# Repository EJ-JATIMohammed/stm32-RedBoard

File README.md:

# STM32 RedBoard

Custom STM32F103C8T6 development board designed with KiCad, featuring USB-C, Micro-USB, CAN, Micro-SD, SWD and GPIO interfaces.

## Overview

The STM32 RedBoard is an open-source hardware development platform built around the ARM Cortex-M3-based STM32F103C8T6 microcontroller. The board integrates multiple connectivity options and interfaces, designed for embedded systems development, prototyping, and educational projects using professional-grade open-source tools.

## Features

- **Microcontroller**: ARM Cortex-M3 STM32F103C8T6 (72 MHz)
- **Memory**: 256 KB Flash, 64 KB SRAM
- **Connectivity**: USB-C and Micro-USB interfaces, CAN 2.0B support, Micro-SD card interface
- **Debugging**: Serial Wire Debug (SWD) interface for real-time debugging and firmware upload
- **Expansion**: GPIO pins for sensor integration and custom applications
- **Design**: Professional schematic and PCB layout in KiCad 10.0

## Hardware Specifications

| Specification | Value |
|---|---|
| Microcontroller | STM32F103C8T6 (ARM Cortex-M3, 72 MHz) |
| Flash Memory | 256 KB |
| SRAM | 64 KB |
| Supply Voltage | 3.3V (USB or external) |
| Interfaces | USB-C, Micro-USB, CAN, SWD, Micro-SD, GPIO |
| EDA Tool | KiCad 10.0 |

## Interfaces

### USB-C (Primary Interface)
USB Type-C 2.0 interface for primary power supply and data communication. Features reversible plug orientation and robust mechanical connection.

### Micro-USB (Secondary Interface)
USB Micro Type-B connector for alternative power and communication. Provides legacy compatibility and additional charging capability.

### CAN Bus
CAN 2.0B protocol support for vehicle diagnostics, industrial automation, and real-time control systems. Uses differential signaling with CAN_H and CAN_L lines.

### Micro-SD Card Interface
8-pin Micro SD Card Socket supporting SDIO/SPI modes. Enables data storage, firmware updates, and data logging applications.

### SWD (Serial Wire Debug)
ARM Serial Wire Debug interface for real-time debugging and firmware programming. Compatible with ST-LINK/V2, Segger J-Link, and OpenOCD-compatible debuggers.

### GPIO Expansion
Multiple GPIO pins from the STM32F103C8T6 with 3.3V logic levels (5V tolerant on selected pins). Supports digital I/O, PWM, analog input (ADC), and timer functions.

## Hardware Design

The STM32 RedBoard is fully designed in **KiCad 10.0**, a professional, open-source electronic design automation suite supporting Windows, macOS, and Linux.

### Design Files

| File | Description |
|---|---|
| `kicad_files/stm32f013 Red board.kicad_sch` | Main schematic with all component connections and interfaces |
| `kicad_files/Block_Diagram.kicad_sch` | High-level system architecture overview |
| `kicad_files/stm32f013 Red board.kicad_pcb` | PCB layout, routing, and component placement |
| `kicad_files/stm32f013 Red board.kicad_pro` | KiCad project file |

## PCB Images

Representative design documentation images:

## Repository Structure

```
stm32-RedBoard/
├── README.md                                        # Project documentation
├── LICENSE                                          # MIT License
├── PCB_images/                                      # Design documentation images
│   ├── 1.png
│   ├── 2.png
│   ├── 3.png
│   ├── 4.png
│   ├── 5.png
│   ├── 6.png
│   └── 7.png
├── Shematics/                                       # Schematic PDF export
│   └── stm32f013 Red board-Stm32_Red_Board.pdf
└── kicad_files/                                     # KiCad project files
    ├── Block_Diagram.kicad_sch
    ├── Stm32_Red_Board.kicad_sch
    ├── stm32f013 Red board.kicad_sch
    ├── stm32f013 Red board.kicad_pcb
    ├── stm32f013 Red board.kicad_pro
    ├── stm32f013 Red board.kicad_prl
    ├── stm32f013 Red board-Stm32_Red_Board.pdf
    └── _restore_backup_*/ (version control backups)
```

## Getting Started

### Prerequisites

- **KiCad 10.0 or later** – Download from [kicad.org](https://www.kicad.org)
- **Git** (optional, for cloning the repository)

### Opening the Project

1. **Clone the repository**
   ```bash
   git clone https://github.com/EJ-JATIMohammed/stm32-RedBoard.git
   cd stm32-RedBoard
   ```

2. **Open in KiCad**
   - Launch KiCad
   - Select **File** → **Open Project**
   - Navigate to `kicad_files/stm32f013 Red board.kicad_pro`

3. **Explore the design**
   - **Schematic**: View connections and component values
   - **PCB Layout**: Review trace routing and layer assignments
   - **Block Diagram**: See `Block_Diagram.kicad_sch` for system overview
   - **3D Viewer**: View → 3D Viewer for mechanical review

### Design Tools

- **Electrical Rules Check (ERC)**: Tools → Electrical Rules Checker
- **Design Rules Check (DRC)**: Tools → Design Rules Checker
- **Manufacturing Files**: File → Plot to generate Gerber files

## Programming and Debugging

### Supported Debuggers

- **ST-LINK/V2** – Official STMicroelectronics debugger
- **Segger J-Link** – Universal JTAG/SWD debugger
- **OpenOCD** – Open-source debugging protocol

### Development Environments

- **STM32CubeIDE** – Official STMicroelectronics IDE
- **STM32CubeMX** – Configuration and code generation
- **VSCode + ARM Toolchain** – Open-source workflow
- **PlatformIO** – Cross-platform embedded development

## Future Improvements

- **Documentation**: Detailed pinout assignments, bill of materials (BOM), assembly guide
- **Firmware Examples**: USB drivers, CAN bus applications, Micro-SD file system integration, GPIO and ADC samples
- **Hardware Validation**: Prototype fabrication and functional testing
- **Design Enhancements**: 3D STEP models, EMC/EMI review, power distribution optimization

## License

This project is released under the **MIT License**. See [LICENSE](LICENSE) for complete terms.

## Author

**EJ-JATI Mohammed**  
GitHub: [EJ-JATIMohammed](https://github.com/EJ-JATIMohammed)  
Repository: [stm32-RedBoard](https://github.com/EJ-JATIMohammed/stm32-RedBoard)

---

**Project Created**: August 2026  
**Last Updated**: October 2026  
**KiCad Version**: 10.0

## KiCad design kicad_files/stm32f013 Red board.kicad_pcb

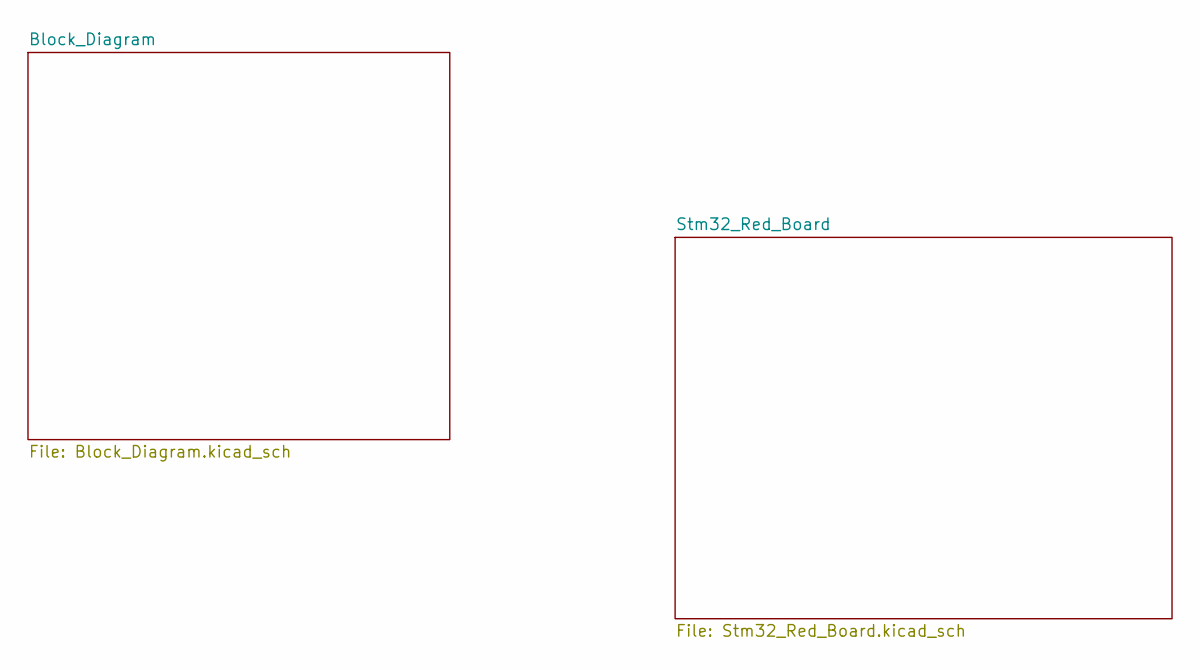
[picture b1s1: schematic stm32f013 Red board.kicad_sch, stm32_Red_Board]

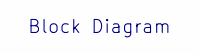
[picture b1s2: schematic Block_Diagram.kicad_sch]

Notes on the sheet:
Block Diagram

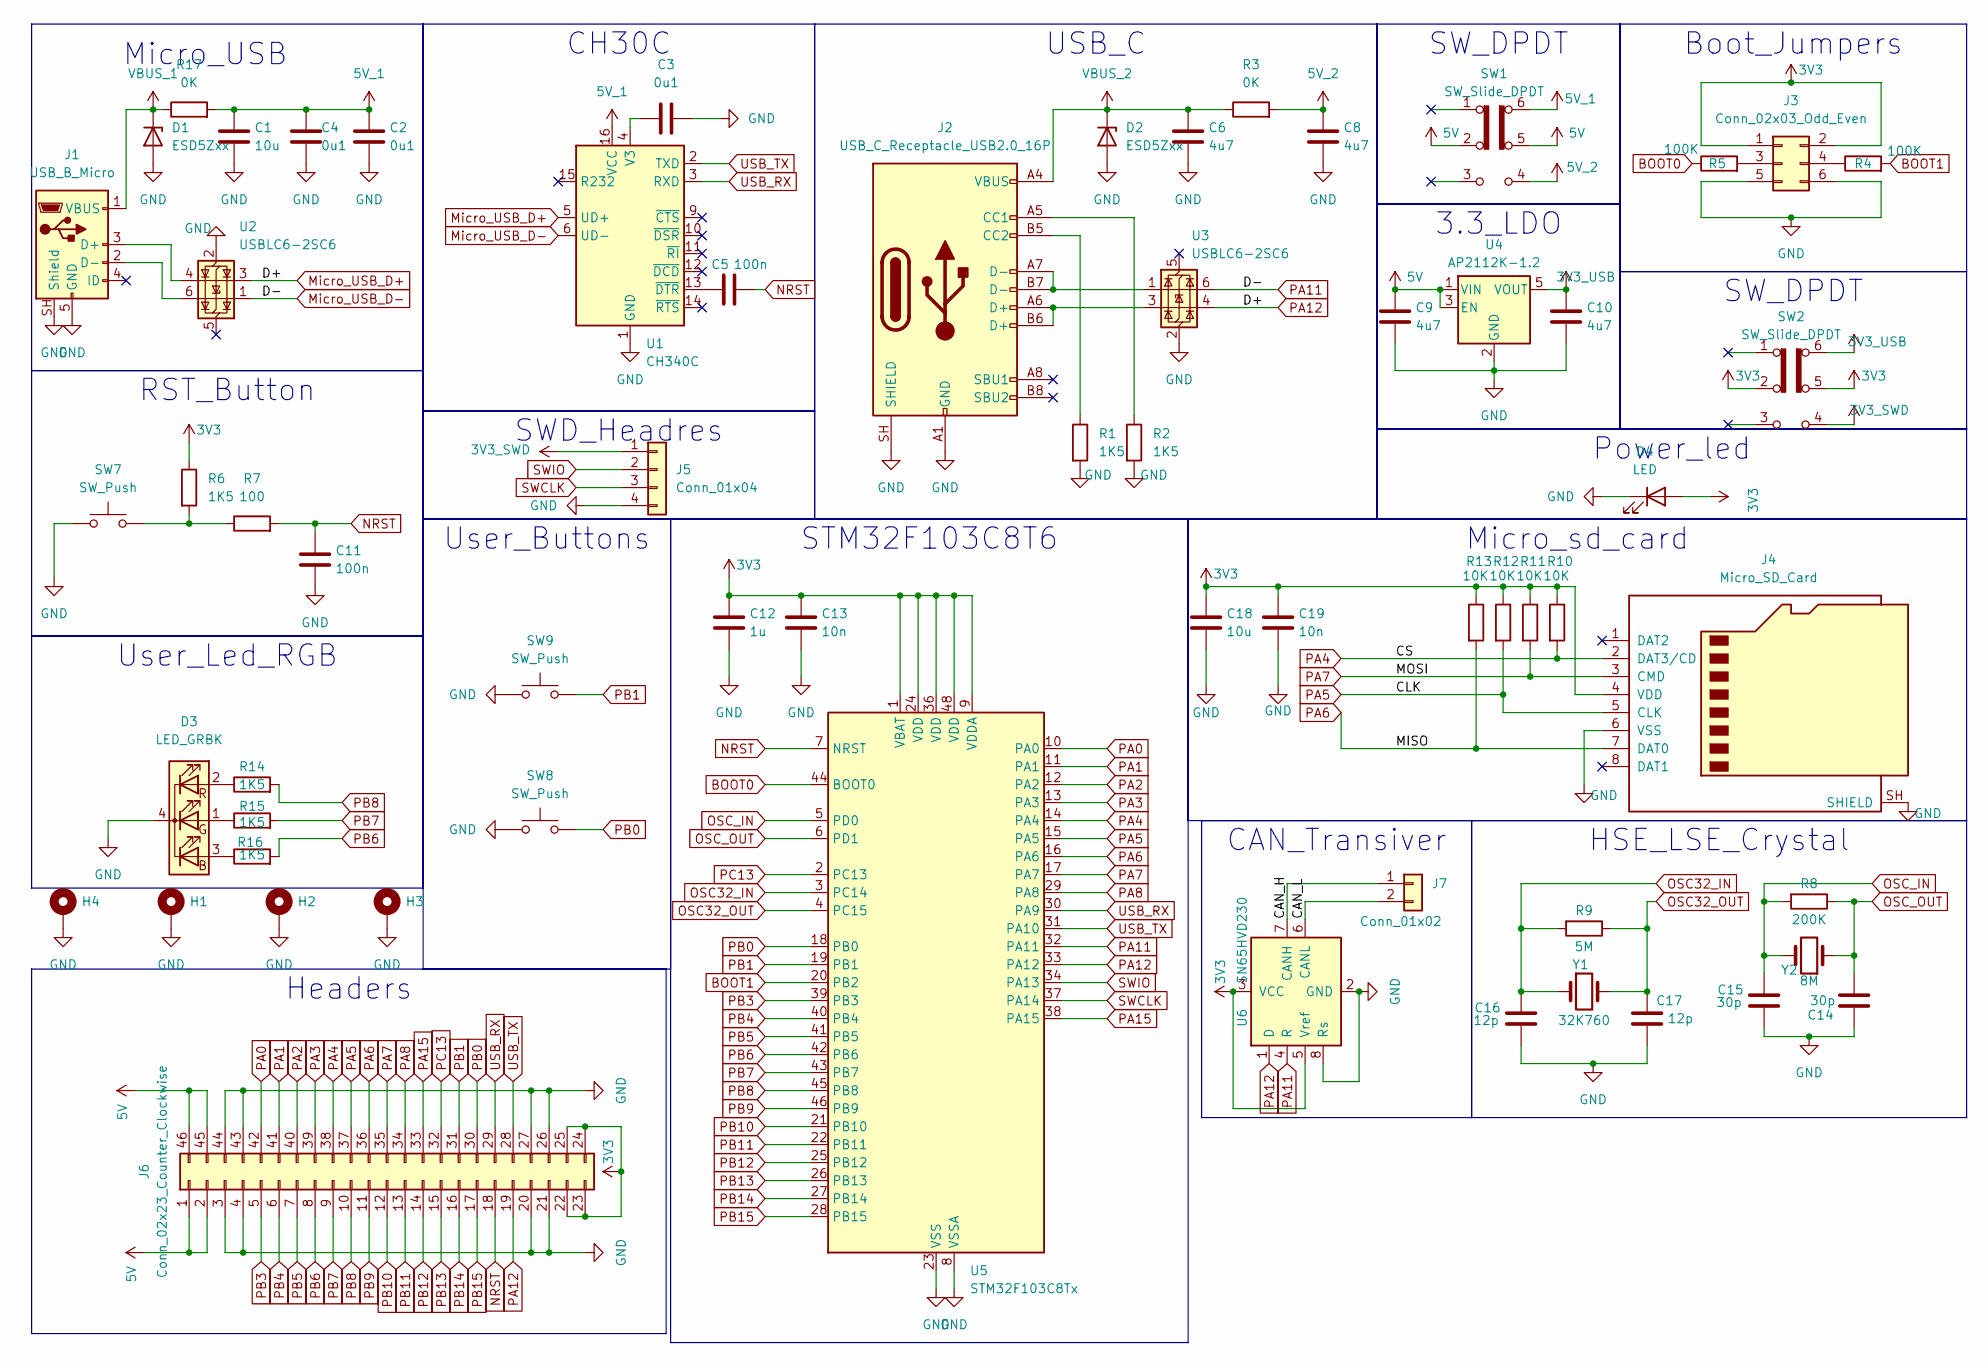
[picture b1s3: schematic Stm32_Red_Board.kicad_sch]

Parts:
C1, C18: 10u; C_0402_1005Metric
C2, C3, C4: 0u1; C_0402_1005Metric
C5, C11: 100n; C_0402_1005Metric
C6, C8, C9, C10: 4u7; C_0402_1005Metric
C12: 1u; C_0402_1005Metric
C13, C19: 10n; C_0402_1005Metric
C14, C15: 30p; C_0402_1005Metric
C16, C17: 12p; C_0402_1005Metric
D1, D2: ESD5Zxx; D_SOD-523
D3: LED_GRBK; LED_ASMB-KTF0-0A306
D4: LED; LED_01005_0402Metric_Pad0.57x0.30mm_HandSolder
H1, H2, H3, H4: MountingHole_Pad; MountingHole_2.5mm_Pad
J1: USB_B_Micro; USB_Micro-B_Molex-105017-0001
J2: USB_C_Receptacle_USB2.0_16P; USB_C_Receptacle_GCT_USB4105-xx-A_16P_TopMnt_Horizontal
J3: Conn_02x03_Odd_Even; PinHeader_2x03_P2.54mm_Vertical
J4: Micro_SD_Card; microSD_HC_Wuerth_693072010801
J5: Conn_01x04; PinHeader_1x04_P2.54mm_Vertical
J6: Conn_02x23_Counter_Clockwise; PinHeader_2x23_P2.54mm_Vertical
J7: Conn_01x02; PinSocket_1x02_P2.54mm_Vertical
R1, R2, R6, R14, R15, R16: 1K5; R_0402_1005Metric
R3, R17: 0K; R_0402_1005Metric
R4, R5: 100K; R_0402_1005Metric
R7: 100; R_0402_1005Metric
R8: 200K; R_0402_1005Metric
R9: 5M; R_0402_1005Metric
R10, R11, R12, R13: 10K; R_0402_1005Metric
SW1, SW2: SW_Slide_DPDT; SW_DPDT_CK_JS202011JCQN
SW7, SW8, SW9: SW_Push; SW_PUSH_6mm_H5mm
U1: CH340C; SOIC-16_3.9x9.9mm_P1.27mm
U2, U3: USBLC6-2SC6; SOT-23-6
U4: AP2112K-1.2; SOT-23-5
U5: STM32F103C8Tx; LQFP-48_7x7mm_P0.5mm
U6: SN65HVD230; SOIC-8_3.9x4.9mm_P1.27mm
Y1: 32K760; Crystal_SMD_SeikoEpson_MC405-2Pin_9.6x4.1mm_HandSoldering
Y2: 8M; Crystal_HC49-4H_Vertical

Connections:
3V3: C12.1, C13.1, C18.1, C19.1, D4.2 (A), J3.1, J3.2, J4.4 (VDD), J6.22, J6.23, J6.24, J6.25, R6.1, R10.1, R11.1, R12.1, R13.1, SW2.2 (B), SW2.5 (B), U5.1 (VBAT), U5.9 (VDDA), U5.24 (VDD), U5.36 (VDD), U5.48 (VDD), U6.3 (VCC), U6.5 (Vref)
3V3_SWD: J5.1, SW2.4 (A)
3V3_USB: C10.1, SW2.6 (C), U4.5 (VOUT)
5V: C9.1, J6.1, J6.2, J6.45, J6.46, SW1.2 (B), SW1.5 (B), U4.1 (VIN), U4.3 (EN)
5V_1: C1.1, C2.1, C4.1, R17.2, SW1.6 (C), U1.16 (VCC)
5V_2: C8.1, R3.2, SW1.4 (A)
/Stm32_Red_Board/CAN_H: J7.1, U6.7 (CANH)
/Stm32_Red_Board/CAN_L: J7.2, U6.6 (CANL)
BOOT0: R5.1, U5.44 (BOOT0)
BOOT1: R4.2, U5.20 (PB2)
GND: C1.2, C2.2, C3.2, C4.2, C6.2, C8.2, C9.2, C10.2, C11.2, C12.2, C13.2, C14.1, C15.1, C16.1, C17.1, C18.2, C19.2, D1.2 (A), D2.2 (A), D3.4 (K), D4.1 (K), H1.1 (1_1), H2.1 (1_1), H3.1 (1_1), H4.1 (1_1), J1.5 (GND), J1.SH (Shield), J2.A1 (GND), J2.A12 (GND), J2.B1 (GND), J2.B12 (GND), J2.SH (SHIELD), J3.5, J3.6, J4.6 (VSS), J4.SH (SHIELD), J5.4, J6.3, J6.4, J6.20, J6.21, J6.26, J6.27, J6.43, J6.44, R1.2, R2.2, SW7.1, SW8.1, SW9.1, U1.1 (GND), U2.2 (GND), U3.2 (GND), U4.2 (GND), U5.8 (VSSA), U5.23 (VSS), U5.35 (VSS), U5.47 (VSS), U6.2 (GND), U6.8 (Rs)
Micro_USB_D+: J6.19, U1.5 (UD+), U2.3 (I/O2), U3.4 (I/O2), U5.33 (PA12), U6.1 (D)
Micro_USB_D-: U1.6 (UD-), U2.1 (I/O1), U3.6 (I/O1), U5.32 (PA11), U6.4 (R)
NRST: C5.2, C11.1, J6.18, R7.2, U5.7 (NRST)
unnamed: D3.3 (BA), R16.1
unnamed: D3.1 (GA), R15.1
unnamed: D3.2 (RA), R14.1
unnamed: J1.3 (D+), U2.4 (I/O2)
unnamed: J1.2 (D-), U2.6 (I/O1)
unnamed: J2.A5 (CC1), R2.1
unnamed: J2.B5 (CC2), R1.1
unnamed: J2.A6 (D+), J2.B6 (D+), U3.3 (I/O2)
unnamed: J2.A7 (D-), J2.B7 (D-), U3.1 (I/O1)
unnamed: J3.3, R5.2
unnamed: J3.4, R4.1
unnamed: R6.2, R7.1, SW7.2
unnamed: C3.1, U1.4 (V3)
unnamed: C5.1, U1.13 (~DTR)
OSC32_IN: C16.2, R9.2, U5.3 (PC14), Y1.1
OSC32_OUT: C17.2, R9.1, U5.4 (PC15), Y1.2
OSC_IN: C15.2, R8.2, U5.5 (PD0), Y2.2
OSC_OUT: C14.2, R8.1, U5.6 (PD1), Y2.1
PA0: J6.42, U5.10 (PA0)
PA1: J6.41, U5.11 (PA1)
PA2: J6.40, U5.12 (PA2)
PA3: J6.39, U5.13 (PA3)
PA4: J4.2 (DAT3/CD), J6.38, R10.2, U5.14 (PA4)
PA5: J4.5 (CLK), J6.37, R12.2, U5.15 (PA5)
PA6: J4.7 (DAT0), J6.36, R13.2, U5.16 (PA6)
PA7: J4.3 (CMD), J6.35, R11.2, U5.17 (PA7)
PA8: J6.34, U5.29 (PA8)
PA15: J6.33, U5.38 (PA15)
PB0: J6.30, SW8.2, U5.18 (PB0)
PB1: J6.31, SW9.2, U5.19 (PB1)
PB3: J6.5, U5.39 (PB3)
PB4: J6.6, U5.40 (PB4)
PB5: J6.7, U5.41 (PB5)
PB6: J6.8, R16.2, U5.42 (PB6)
PB7: J6.9, R15.2, U5.43 (PB7)
PB8: J6.10, R14.2, U5.45 (PB8)
PB9: J6.11, U5.46 (PB9)
PB10: J6.12, U5.21 (PB10)
PB11: J6.13, U5.22 (PB11)
PB12: J6.14, U5.25 (PB12)
PB13: J6.15, U5.26 (PB13)
PB14: J6.16, U5.27 (PB14)
PB15: J6.17, U5.28 (PB15)
PC13: J6.32, U5.2 (PC13)
SWCLK: J5.3, U5.37 (PA14)
SWIO: J5.2, U5.34 (PA13)
USB_RX: J6.29, U1.3 (RXD), U5.30 (PA9)
USB_TX: J6.28, U1.2 (TXD), U5.31 (PA10)
VBUS_1: D1.1 (K), J1.1 (VBUS), R17.1
VBUS_2: C6.1, D2.1 (K), J2.A4 (VBUS), J2.A9 (VBUS), J2.B4 (VBUS), J2.B9 (VBUS), R3.1

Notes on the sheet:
Micro_USB
Headers
Power_led
RST_Button
CH30C
SW_DPDT
User_Buttons
STM32F103C8T6
3.3_LDO
CAN_Transiver
HSE_LSE_Crystal
User_Led_RGB
Micro_sd_card
SWD_Headres
Boot_Jumpers
USB_C

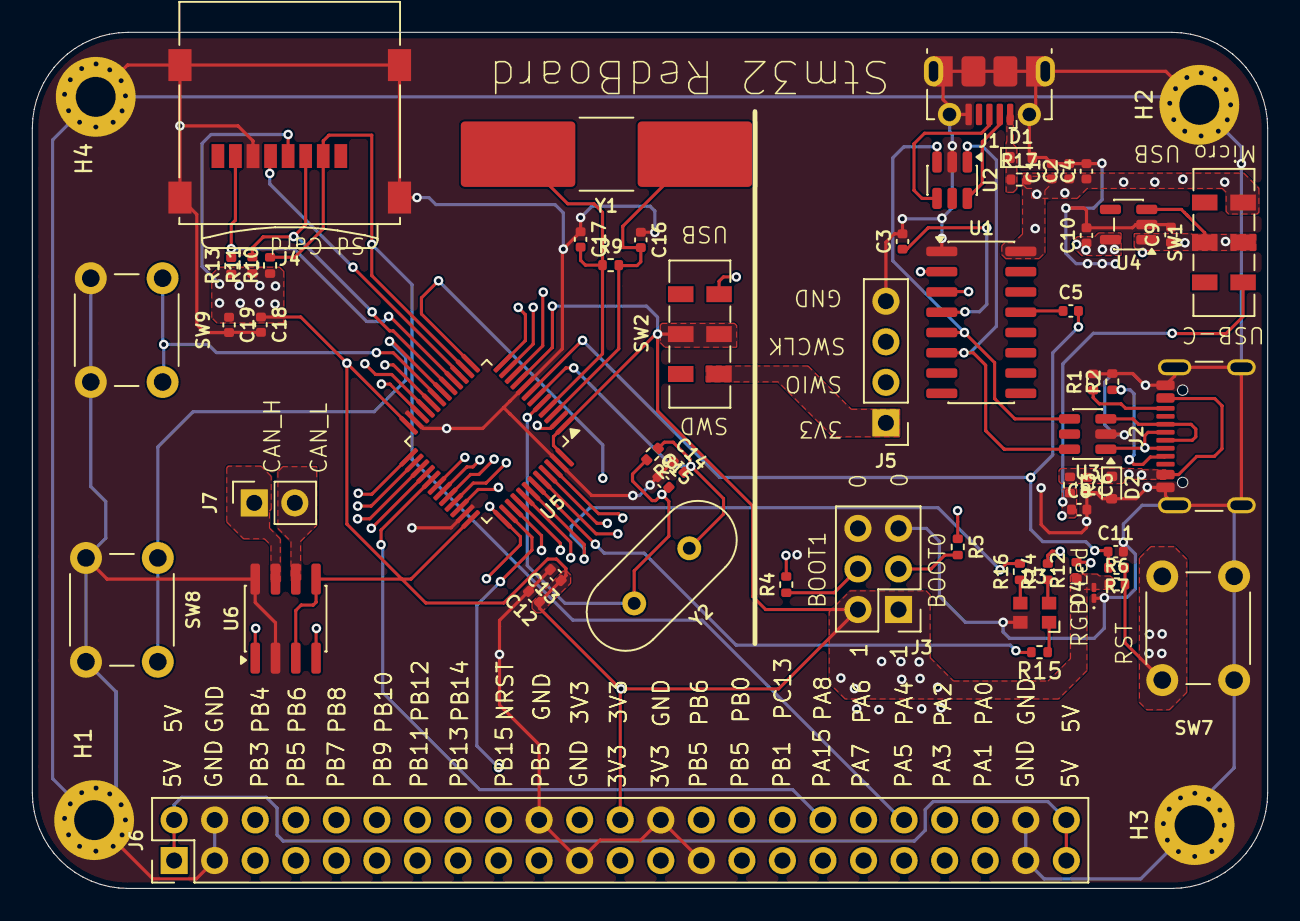
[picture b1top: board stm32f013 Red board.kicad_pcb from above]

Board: 8 copper layers, 77.4 x 53.6 mm, 63 parts (0 on the bottom side), 64 nets.
